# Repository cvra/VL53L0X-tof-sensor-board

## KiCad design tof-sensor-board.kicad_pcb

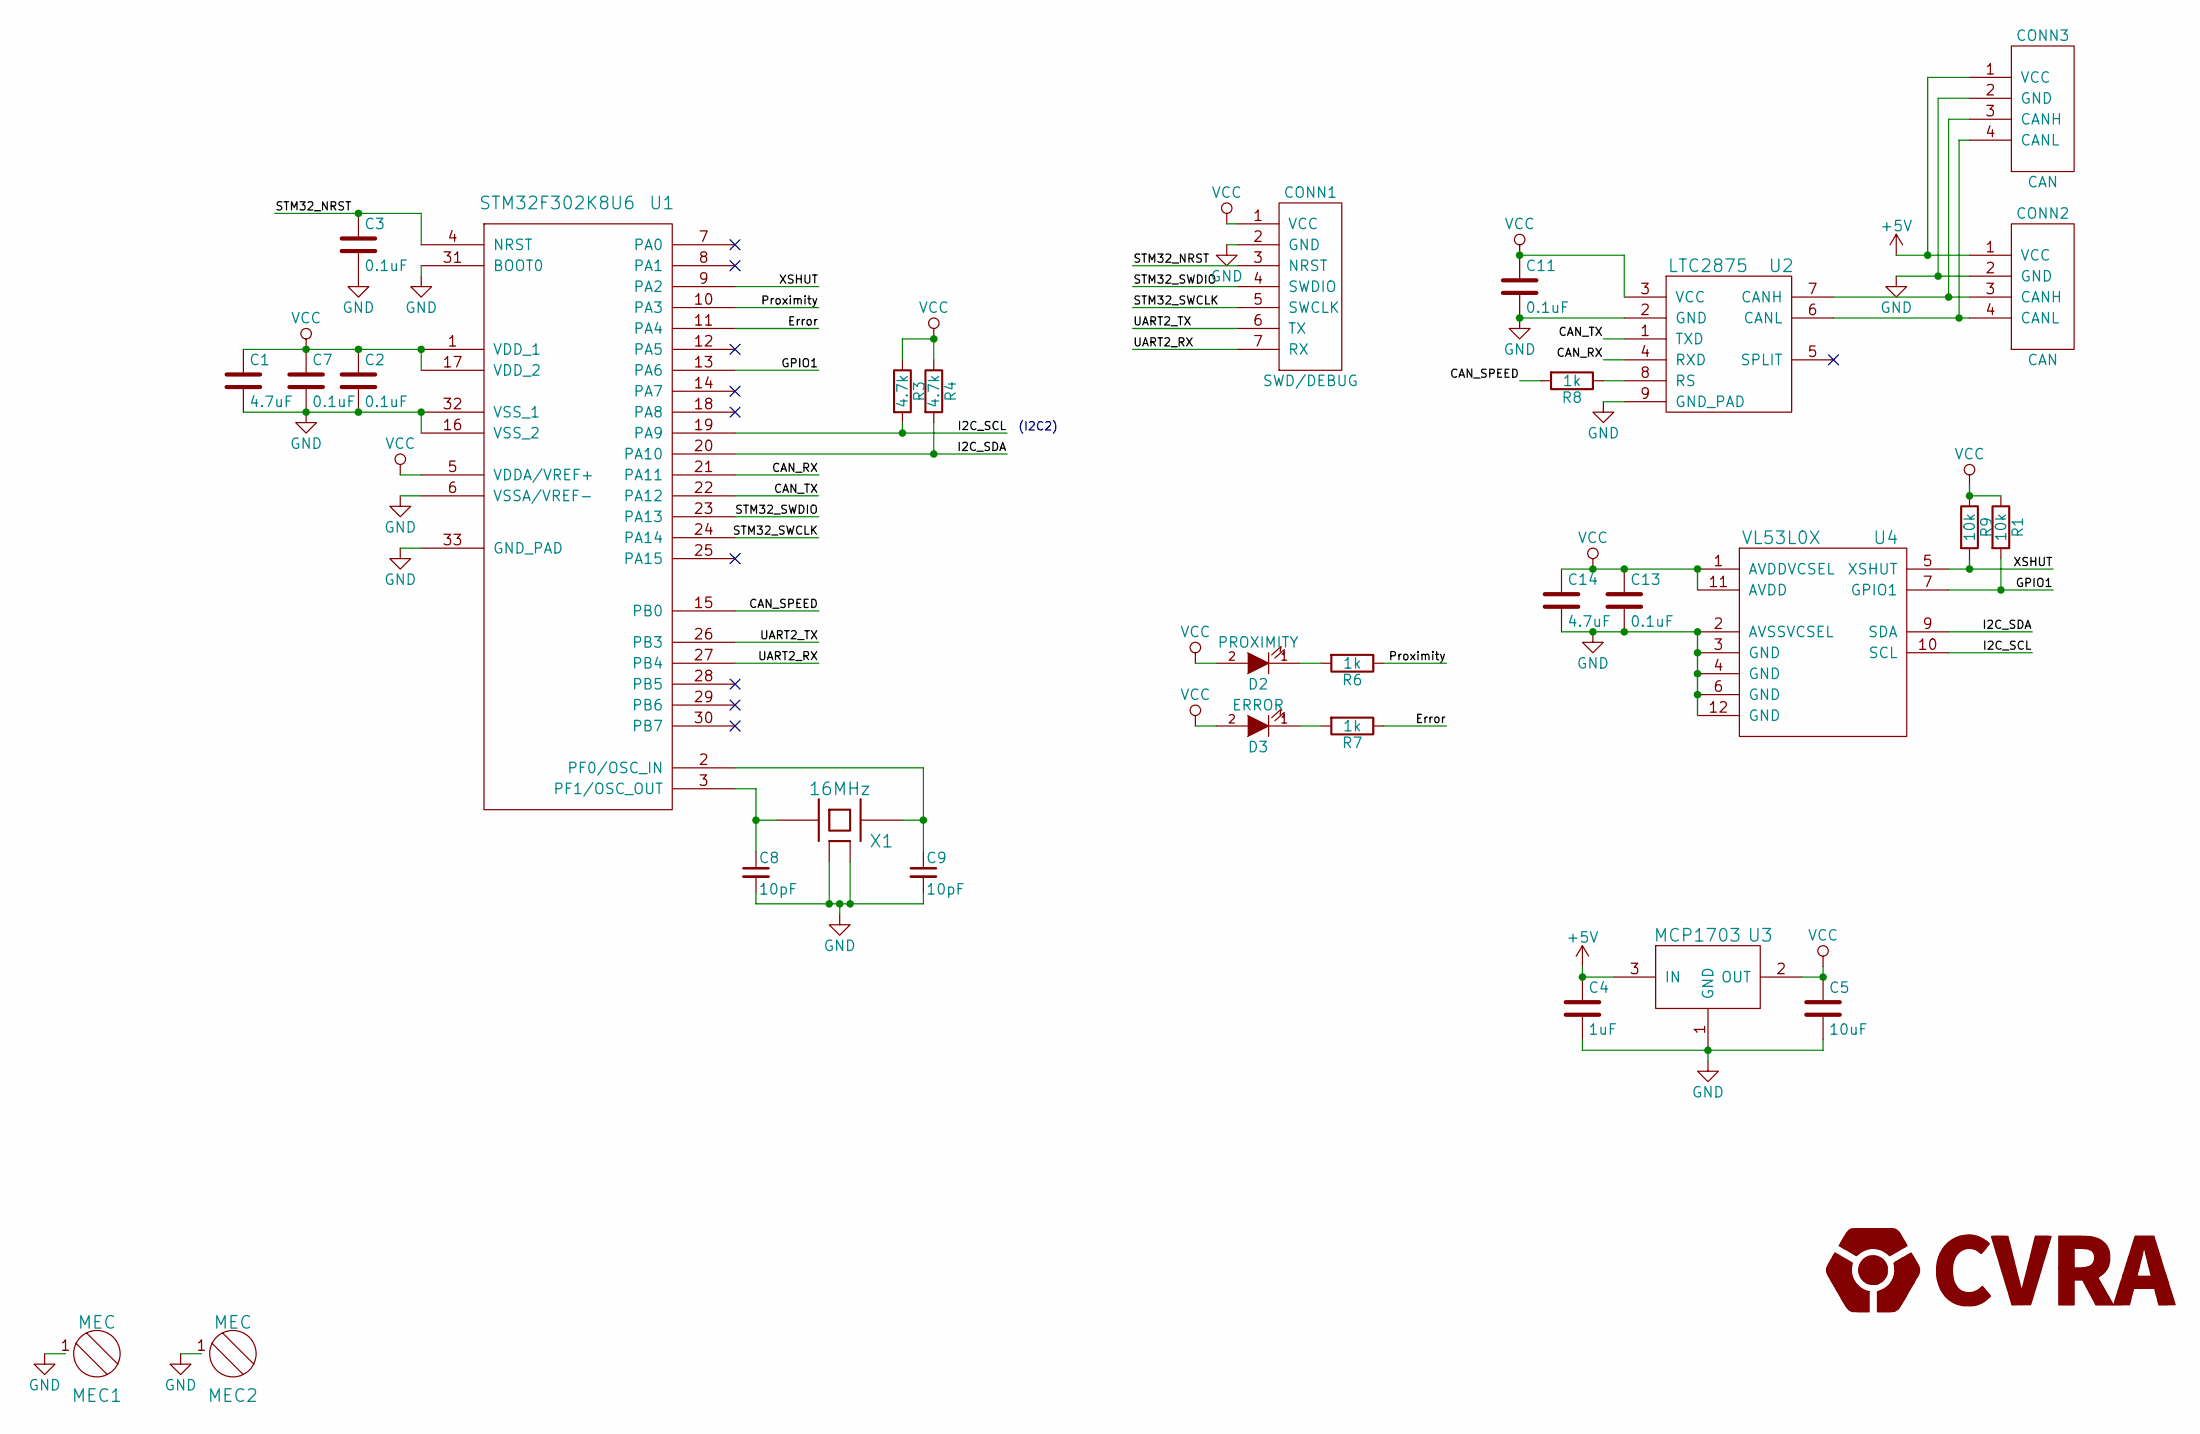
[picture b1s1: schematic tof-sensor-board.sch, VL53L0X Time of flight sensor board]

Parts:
C1, C14: 4.7uF; C_0603
C2, C3, C7, C11, C13: 0.1uF; C_0402
C4: 1uF; C_0603
C5: 10uF; C_0603
C8, C9: 10pF; C_0402
CONN1: SWD/DEBUG; Connector_Molex_PicoBlade_53047-0710
CONN2, CONN3: CAN; _Molex-PicoBlade-SMD-4
D2: PROXIMITY; R_0603
D3: ERROR; R_0603
MEC1, MEC2: MEC; _M2
R1, R9: 10k; R_0402
R3, R4: 4.7k; R_0402
R6, R7, R8: 1k; R_0402
U1: STM32F302K8U6; QFN-32-1EP_5x5mm_Pitch0.5mm
U2: LTC2875; DFN-8-1EP_3x3mm_Pitch0.5mm
U3: MCP1703; SOT-23
U4: VL53L0X
X1: 16MHz; _TSX-3225-SMD-XTAL

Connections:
+5V: C4.1, CONN2.1 (VCC), CONN3.1 (VCC), U3.3 (IN)
/CAN_RX: U1.21 (PA11), U2.4 (RXD)
/CAN_SPEED: R8.2, U1.15 (PB0)
/CAN_TX: U1.22 (PA12), U2.1 (TXD)
/Error: R7.1, U1.11 (PA4)
/GPIO1: R1.2, U1.13 (PA6), U4.7 (GPIO1)
/I2C_SCL: R3.2, U1.19 (PA9), U4.10 (SCL)
/I2C_SDA: R4.2, U1.20 (PA10), U4.9 (SDA)
/Proximity: R6.1, U1.10 (PA3)
/STM32_NRST: C3.1, CONN1.3 (NRST), U1.4 (NRST)
/STM32_SWCLK: CONN1.5 (SWCLK), U1.24 (PA14)
/STM32_SWDIO: CONN1.4 (SWDIO), U1.23 (PA13)
/UART2_RX: CONN1.7 (RX), U1.27 (PB4)
/UART2_TX: CONN1.6 (TX), U1.26 (PB3)
/XSHUT: R9.2, U1.9 (PA2), U4.5 (XSHUT)
GND: C1.2, C2.2, C3.2, C4.2, C5.2, C7.2, C8.2, C9.2, C11.2, C13.2, C14.2, CONN1.2 (GND), CONN2.2 (GND), CONN2.MECH (GND), CONN3.2 (GND), CONN3.MECH (GND), MEC1.1, MEC2.1, U1.6 (VSSA/VREF-), U1.16 (VSS_2), U1.31 (BOOT0), U1.32 (VSS_1), U1.33 (GND_PAD), U2.2 (GND), U2.9 (GND_PAD), U3.1 (GND), U4.2 (AVSSVCSEL), U4.3 (GND), U4.4 (GND), U4.6 (GND), U4.12 (GND), X1.2 (case), X1.4 (case)
unnamed: C8.1, U1.3 (PF1/OSC_OUT), X1.1
unnamed: C9.1, U1.2 (PF0/OSC_IN), X1.3
unnamed: CONN2.3 (CANH), CONN3.3 (CANH), U2.7 (CANH)
unnamed: CONN2.4 (CANL), CONN3.4 (CANL), U2.6 (CANL)
unnamed: D2.1 (K), R6.2
unnamed: D3.1 (K), R7.2
unnamed: R8.1, U2.8 (RS)
VCC: C1.1, C2.1, C5.1, C7.1, C11.1, C13.1, C14.1, CONN1.1 (VCC), D2.2 (A), D3.2 (A), R1.1, R3.1, R4.1, R9.1, U1.1 (VDD_1), U1.5 (VDDA/VREF+), U1.17 (VDD_2), U2.3 (VCC), U3.2 (OUT), U4.1 (AVDDVCSEL), U4.11 (AVDD)

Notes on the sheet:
(I2C2)

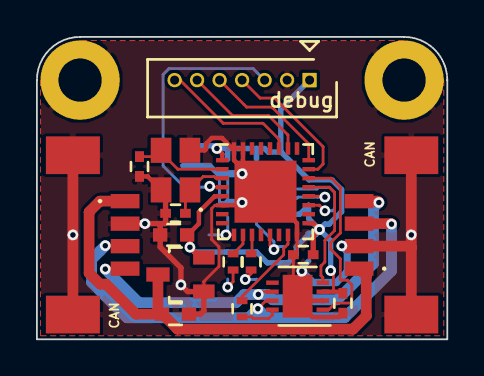
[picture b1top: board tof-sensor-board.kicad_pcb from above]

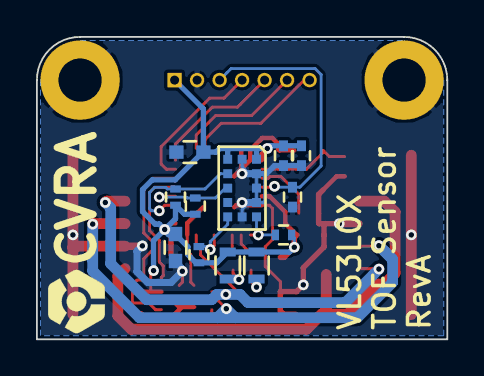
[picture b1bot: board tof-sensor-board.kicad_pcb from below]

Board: 2 copper layers, 22.8 x 16.8 mm, 30 parts (12 on the bottom side), 24 nets.

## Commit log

2015-05-29 Add KiCad library
2015-05-29 Datasheets
2015-06-16 Schematic (done)
2015-06-16 Plot schematic to PDF
2015-06-16 Duplicate CAN connector to allow daisy chain wiring
2015-07-04 Netlist
2015-07-04 Components footprints
2016-05-31 Switch to VL53L0X and QFN32 STM32f302
2016-06-06 Fix I2C connection, remove power LED
2016-07-24 Start placing footprints
2016-07-24 LDO footprint, fix unconnected GND pin
2016-07-24 Place mounting holes
2016-07-25 elongated shape with connectors on same edge
2016-07-25 mounting holes on same edge
2016-08-29 routing
2016-08-31 routing finished
2016-08-31 update doc
2016-08-31 set solder stop mask and solder paste clearance
2016-09-01 gerber files
2016-09-01 annotate sensor position
2016-09-06 Review changes
    changes from Rouven's review:
    - fix silkscreen too close to pad
    - increase CAN and 5V trace width
    - make LEDs common VCC
    - route voltage regulator 5V input through cpacitor
    - add debug connector label
